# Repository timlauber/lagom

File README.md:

# lagom
Lagom is an easy to build 65% keyboard using ~~only~~ some through hole components. It uses a separate microcontroller (like the Pro Micro, Elite C or something RP2040 based) to enable flexibility in firmware and connectivity and to further simplify the soldering experience (no more tricksy USB ports). Demultiplexers and a custom matrix are used to enable the size and features of the board with only the pinouts of a pro micro.

## Changes
This version replaces most trough hole components for SMD variants, but keeps visuals. A power switch as well as a battery connector is added for full wireless support. Only ISO layout is supported.

**Original lagom kits are available for sale at [sthlmkb.com](https://sthlmkb.com/shop/lagom-keyboard-kit/)**

[License](LICENSE)

Lagom is licensed under the [Creative Commons Attribution-NonCommercial 4.0 International license](https://creativecommons.org/licenses/by-nc/4.0/). This design as it stands in this repository may be freely reproduced, modified, and manufactured for PERSONAL USE ONLY and may not be reproduced in physical form for public sale. 

## Features
* ~~Only through hole components for easy soldering~~
* Separate microcontroller using Pro micro, Elite C, Nice! Nano or equivalent footprint. So micro USB, USB-C or Bluetooth are all options!
* 2 rotary encoders
* OLED screen
* Optional underglow RGB lighting with a WS2812b light strip
* ~~Multiple layout options including ISO, ANSI, split space (2.25u + 1.25u + 2.75u), 7u space, split left shift (1.25u + 1u) and stepped capslock ([layout]("http://www.keyboard-layout-editor.com/##@_name=Lagom&notes=16%20cols%20%2F=%204%20pins%20with%202x%203%20to%208%20demux%20(2%5E4%20%2F=%2016)%0A5%20rows%0A11%20pins%20total%20for%20keyswitches%0A16%20+%202%20pins%20(for%20OLED)%20on%20a%20pro%20micro%0A1%20pin%20for%20LED%20underglow%0A4%20pins%20for%202%20encoders%0A%0A72%20keys%20+%202%20enc%20%3B&@_x:13.75%3B&=1,15&_x:0.25%3B&=2,15&_x:0.25%3B&=0,0%0A%0A%0A%0A%0A%0A%0A%0A%0Ae&=0,1%0A%0A%0A%0A%0A%0A%0A%0A%0Ae%3B&@_y:0.25%3B&=0,0&=0,1&=0,2&=0,3&=0,4&=0,5&=0,6&=0,7&=0,8&=0,9&=0,10&=0,11&=0,12&_w:2%3B&=0,14%0A%0A%0A0,0&=0,15&_x:0.25%3B&=1,0%0A%0A%0A%0A%0A%0A%0A%0A%0Ae&=1,1%0A%0A%0A%0A%0A%0A%0A%0A%0Ae%3B&@_w:1.5%3B&=1,0&=1,1&=1,2&=1,3&=1,4&=1,5&=1,6&=1,7&=1,8&=1,9&=1,10&=1,11&=1,12&_w:1.5%3B&=1,13%0A%0A%0A1,0&=1,14%3B&@_w:1.75%3B&=2,0&=2,1&=2,2&=2,3&=2,4&=2,5&=2,6&=2,7&=2,8&=2,9&=2,10&=2,11&_w:2.25%3B&=2,13%0A%0A%0A1,0&=2,14%3B&@_w:2.25%3B&=3,0%0A%0A%0A2,0&=3,2&=3,3&=3,4&=3,5&=3,6&=3,7&=3,8&=3,9&=3,10&=3,11&_w:1.75%3B&=3,12&=3,13&=3,14%3B&@_w:1.25%3B&=4,0%0A%0A%0A3,0&_w:1.25%3B&=4,1%0A%0A%0A3,0&_w:1.25%3B&=4,2%0A%0A%0A3,0&_w:6.25%3B&=4,6%0A%0A%0A3,0&_w:1.25%3B&=4,10%0A%0A%0A3,0&_w:1.25%3B&=4,11%0A%0A%0A3,0&_x:0.5%3B&=4,12&=4,13&=4,14%3B&@_y:0.5&w:1.25%3B&=4,0%0A%0A%0A3,1&_w:1.25%3B&=4,1%0A%0A%0A3,1&_w:1.25%3B&=4,2%0A%0A%0A3,1&_w:2.25%3B&=4,4%0A%0A%0A3,1&_w:1.25%3B&=4,6%0A%0A%0A3,1&_w:2.75%3B&=4,8%0A%0A%0A3,1&_w:1.25%3B&=4,10%0A%0A%0A3,1&_w:1.25%3B&=4,11%0A%0A%0A3,1%3B&@_y:-0.25&x:15&w:1.25&h:2&w2:1.5&h2:1&x2:-0.25%3B&=2,13%0A%0A%0A1,1%3B&@_y:-0.75&w:1.5%3B&=4,0%0A%0A%0A3,2&=4,1%0A%0A%0A3,2&_w:1.5%3B&=4,2%0A%0A%0A3,2&_w:7%3B&=4,6%0A%0A%0A3,2&_w:1.5%3B&=4,11%0A%0A%0A3,2%3B&@_y:-0.25&x:14%3B&=2,12%0A%0A%0A1,1%3B&@_w:1.25%3B&=3,0%0A%0A%0A2,1&=3,1%0A%0A%0A2,1&_x:9.75%3B&=0,13%0A%0A%0A0,1&=0,14%0A%0A%0A0,1"))~~
* Open and visible components (in the style of Plaid, Romac etc)
* Simple, beautiful and flexible sandwich case out of FR4 (pcb material)

## Components required - To be determined!
* PCB
* FR4 Switch plate
* FR4 Base 
* Controller (I used a Pro Micro in the guide but anything that shares the footprint and pinout will be fine e.g. Elite C, Nice! Nano, or something RP2040 powered!)
* Diodes 1N4148 (74)
* 0.1μF Capacitor (2)
* 16 pin IC socket (2)
* IC (74HC138N) demultiplexer (2)
* Switches (5 pin MX footprint) (up to 72 depending on layout)
* Rotary encoders (2)
* Rotary encoder knobs (2)
* 0.91" OLED screen
* 10mm M2 Standoffs (9 required if mounting the base to the plate)
* 6mm x M2 screws for attaching the standoffs to the plate/base (2 per standoff so 18 total)
* Acrylic cover for the components at the top (optional, not included)
* Stabilisers (PCB mount) (5 x 2u or 3 x 2u + 6.25u or 3 x 2u + 7u depending on layout)
* Rubber feet for the base

Build guide for this version is not available.
[Original build guide available here](https://github.com/mohoyt/lagom/blob/main/build_guide.md)

## Known issues 
None yet! 

## Where to buy
Lagom kits are available for sale exclusively at [sthlmkb.com](https://sthlmkb.com/shop/lagom-keyboard-kit/)

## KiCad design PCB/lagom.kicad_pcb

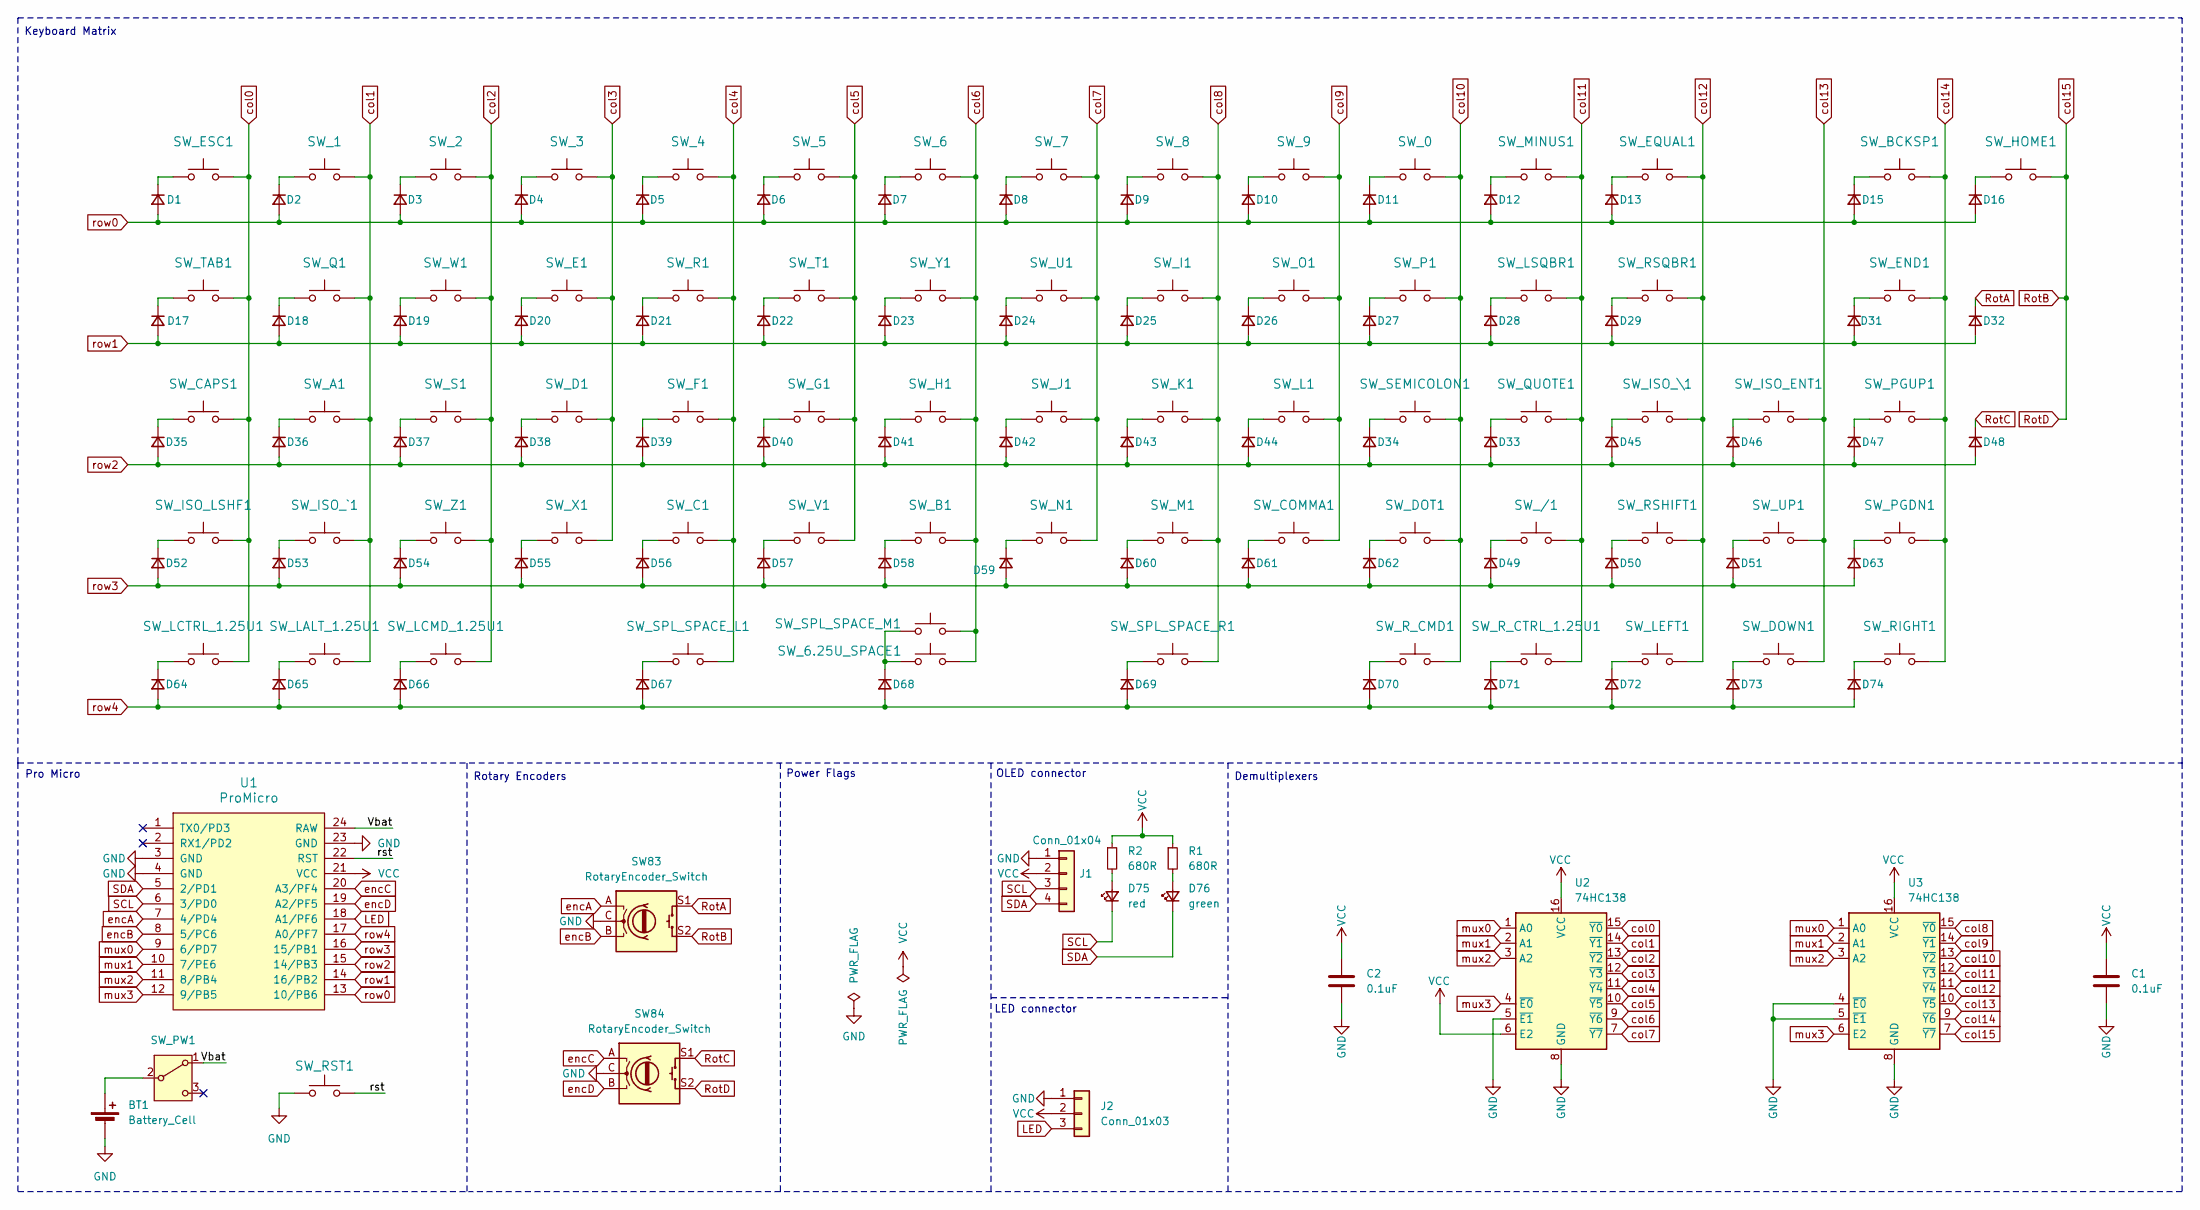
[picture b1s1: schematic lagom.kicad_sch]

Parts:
BT1: Battery_Cell; JST_PH_S2B-PH-K_1x02_P2.00mm_Horizontal
C1, C2: 0.1uF; C_0805_2012Metric
D1, D2, D3, D4, D5, D6, D7, D8, D9, D10, D11, D12, D13, D15, D16, D17, D18, D19, D20, D21, D22, D23, D24, D25, D26, D27, D28, D29, D31, D32, D33, D34, D35, D36, D37, D38, D39, D40, D41, D42, D43, D44, D45, D46, D47, D48, D49, D50, D51, D52, D53, D54, D55, D56, D57, D58, D59, D60, D61, D62, D63, D64, D65, D66, D67, D68, D69, D70, D71, D72, D73, D74: 1N4148; D_MiniMELF_noSilk
D75: red; LED_1206_3216Metric
D76: green; LED_1206_3216Metric
J1: Conn_01x04; PinSocket_1x04_P2.54mm_Vertical
J2: Conn_01x03; PinSocket_1x03_P2.54mm_Vertical
R1, R2: 680R; R_1206_3216Metric
SW83, SW84: RotaryEncoder_Switch; RotaryEncoder_Alps_EC11E-Switch_Vertical_H20mm
SW_0, SW_1, SW_2, SW_3, SW_4, SW_5, SW_6, SW_7, SW_8, SW_9: KEYSW; SW_Kailh_HotSwap_1.00u_PCB
SW_6.25U_SPACE1: KEYSW; SW_Kailh_HotSwap_6.25u_PCB_reverse
SW_/1: KEYSW; SW_Kailh_HotSwap_1.00u_PCB
SW_A1: KEYSW; SW_Kailh_HotSwap_1.00u_PCB
SW_B1: KEYSW; SW_Kailh_HotSwap_1.00u_PCB
SW_BCKSP1: KEYSW; SW_Kailh_HotSwap_2.00u_PCB
SW_C1: KEYSW; SW_Kailh_HotSwap_1.00u_PCB
SW_CAPS1: KEYSW; SW_Kailh_HotSwap_1.75u_PCB
SW_COMMA1: KEYSW; SW_Kailh_HotSwap_1.00u_PCB
SW_D1: KEYSW; SW_Kailh_HotSwap_1.00u_PCB
SW_DOT1: KEYSW; SW_Kailh_HotSwap_1.00u_PCB
SW_DOWN1: KEYSW; SW_Kailh_HotSwap_1.00u_PCB
SW_E1: KEYSW; SW_Kailh_HotSwap_1.00u_PCB
SW_END1: KEYSW; SW_Kailh_HotSwap_1.00u_PCB
SW_EQUAL1: KEYSW; SW_Kailh_HotSwap_1.00u_PCB
SW_ESC1: KEYSW; SW_Kailh_HotSwap_1.00u_PCB
SW_F1: KEYSW; SW_Kailh_HotSwap_1.00u_PCB
SW_G1: KEYSW; SW_Kailh_HotSwap_1.00u_PCB
SW_H1: KEYSW; SW_Kailh_HotSwap_1.00u_PCB
SW_HOME1: KEYSW; SW_Kailh_HotSwap_1.00u_PCB
SW_I1: KEYSW; SW_Kailh_HotSwap_1.00u_PCB
SW_ISO_ENT1: KEYSW; SW_Kailh_HotSwap_ISOEnter_PCB
SW_ISO_LSHF1: KEYSW; SW_Kailh_HotSwap_1.25u_PCB
SW_ISO_\1: KEYSW; SW_Kailh_HotSwap_1.00u_PCB
SW_ISO_`1: KEYSW; SW_Kailh_HotSwap_1.00u_PCB
SW_J1: KEYSW; SW_Kailh_HotSwap_1.00u_PCB
SW_K1: KEYSW; SW_Kailh_HotSwap_1.00u_PCB
SW_L1: KEYSW; SW_Kailh_HotSwap_1.00u_PCB
SW_LALT_1.25U1: KEYSW; SW_Kailh_HotSwap_1.25u_PCB
SW_LCMD_1.25U1: KEYSW; SW_Kailh_HotSwap_1.25u_PCB
SW_LCTRL_1.25U1: KEYSW; SW_Kailh_HotSwap_1.25u_PCB
SW_LEFT1: KEYSW; SW_Kailh_HotSwap_1.00u_PCB
SW_LSQBR1: KEYSW; SW_Kailh_HotSwap_1.00u_PCB
SW_M1: KEYSW; SW_Kailh_HotSwap_1.00u_PCB
SW_MINUS1: KEYSW; SW_Kailh_HotSwap_1.00u_PCB
SW_N1: KEYSW; SW_Kailh_HotSwap_1.00u_PCB
SW_O1: KEYSW; SW_Kailh_HotSwap_1.00u_PCB
SW_P1: KEYSW; SW_Kailh_HotSwap_1.00u_PCB
SW_PGDN1: KEYSW; SW_Kailh_HotSwap_1.00u_PCB
SW_PGUP1: KEYSW; SW_Kailh_HotSwap_1.00u_PCB
SW_PW1: SW_SPDT; PinHeader_1x03_P2.54mm_Vertical
SW_Q1: KEYSW; SW_Kailh_HotSwap_1.00u_PCB
SW_QUOTE1: KEYSW; SW_Kailh_HotSwap_1.00u_PCB
SW_R1: KEYSW; SW_Kailh_HotSwap_1.00u_PCB
SW_RIGHT1: KEYSW; SW_Kailh_HotSwap_1.00u_PCB
SW_RSHIFT1: KEYSW; SW_Kailh_HotSwap_1.75u_PCB
SW_RSQBR1: KEYSW; SW_Kailh_HotSwap_1.00u_PCB
SW_RST1: KEYSW; SW_PUSH_1P1T_6x3.5mm_H5.0_APEM_MJTP1250
SW_R_CMD1: KEYSW; SW_Kailh_HotSwap_1.25u_PCB
SW_R_CTRL_1.25U1: KEYSW; SW_Kailh_HotSwap_1.25u_PCB
SW_S1: KEYSW; SW_Kailh_HotSwap_1.00u_PCB
SW_SEMICOLON1: KEYSW; SW_Kailh_HotSwap_1.00u_PCB
SW_SPL_SPACE_L1: KEYSW; SW_Kailh_HotSwap_2.25u_PCB_reverse
SW_SPL_SPACE_M1: KEYSW; SW_Kailh_HotSwap_1.25u_PCB
SW_SPL_SPACE_R1: KEYSW; SW_Kailh_HotSwap_2.75u_PCB_reverse
SW_T1: KEYSW; SW_Kailh_HotSwap_1.00u_PCB
SW_TAB1: KEYSW; SW_Kailh_HotSwap_1.50u_PCB
SW_U1: KEYSW; SW_Kailh_HotSwap_1.00u_PCB
SW_UP1: KEYSW; SW_Kailh_HotSwap_1.00u_PCB
SW_V1: KEYSW; SW_Kailh_HotSwap_1.00u_PCB
SW_W1: KEYSW; SW_Kailh_HotSwap_1.00u_PCB
SW_X1: KEYSW; SW_Kailh_HotSwap_1.00u_PCB
SW_Y1: KEYSW; SW_Kailh_HotSwap_1.00u_PCB
SW_Z1: KEYSW; SW_Kailh_HotSwap_1.00u_PCB
U1: ProMicro; ArduinoProMicro-ZigZag
U2, U3: 74HC138; SOIC-16_3.9x9.9mm_P1.27mm

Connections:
/Vbat: SW_PW1.1 (A), U1.24 (RAW)
/rst: SW_RST1.2, U1.22 (RST)
GND: BT1.2 (-), C1.2, C2.2, J1.1, J2.1, SW83.C, SW84.C, SW_RST1.1, U1.3 (GND), U1.4 (GND), U1.23 (GND), U2.5 (~E1), U2.8 (GND), U3.4 (~E0), U3.5 (~E1), U3.8 (GND)
LED: J2.3, U1.18 (A1/PF6)
unnamed: BT1.1 (+), SW_PW1.2 (B)
unnamed: D1.1 (K), SW_ESC1.1
unnamed: D2.1 (K), SW_1.1
unnamed: D3.1 (K), SW_2.1
unnamed: D4.1 (K), SW_3.1
unnamed: D5.1 (K), SW_4.1
unnamed: D6.1 (K), SW_5.1
unnamed: D7.1 (K), SW_6.1
unnamed: D8.1 (K), SW_7.1
unnamed: D9.1 (K), SW_8.1
unnamed: D10.1 (K), SW_9.1
unnamed: D11.1 (K), SW_0.1
unnamed: D12.1 (K), SW_MINUS1.1
unnamed: D13.1 (K), SW_EQUAL1.1
unnamed: D15.1 (K), SW_BCKSP1.1
unnamed: D16.1 (K), SW_HOME1.1
unnamed: D17.1 (K), SW_TAB1.1
unnamed: D18.1 (K), SW_Q1.1
unnamed: D19.1 (K), SW_W1.1
unnamed: D20.1 (K), SW_E1.1
unnamed: D21.1 (K), SW_R1.1
unnamed: D22.1 (K), SW_T1.1
unnamed: D23.1 (K), SW_Y1.1
unnamed: D24.1 (K), SW_U1.1
unnamed: D25.1 (K), SW_I1.1
unnamed: D26.1 (K), SW_O1.1
unnamed: D27.1 (K), SW_P1.1
unnamed: D28.1 (K), SW_LSQBR1.1
unnamed: D29.1 (K), SW_RSQBR1.1
unnamed: D31.1 (K), SW_END1.1
unnamed: D33.1 (K), SW_QUOTE1.1
unnamed: D34.1 (K), SW_SEMICOLON1.1
unnamed: D35.1 (K), SW_CAPS1.1
unnamed: D36.1 (K), SW_A1.1
unnamed: D37.1 (K), SW_S1.1
unnamed: D38.1 (K), SW_D1.1
unnamed: D39.1 (K), SW_F1.1
unnamed: D40.1 (K), SW_G1.1
unnamed: D41.1 (K), SW_H1.1
unnamed: D42.1 (K), SW_J1.1
unnamed: D43.1 (K), SW_K1.1
unnamed: D44.1 (K), SW_L1.1
unnamed: D45.1 (K), SW_ISO_\1.1
unnamed: D46.1 (K), SW_ISO_ENT1.1
unnamed: D47.1 (K), SW_PGUP1.1
unnamed: D49.1 (K), SW_/1.1
unnamed: D50.1 (K), SW_RSHIFT1.1
unnamed: D51.1 (K), SW_UP1.1
unnamed: D52.1 (K), SW_ISO_LSHF1.1
unnamed: D53.1 (K), SW_ISO_`1.1
unnamed: D54.1 (K), SW_Z1.1
unnamed: D55.1 (K), SW_X1.1
unnamed: D56.1 (K), SW_C1.1
unnamed: D57.1 (K), SW_V1.1
unnamed: D58.1 (K), SW_B1.1
unnamed: D59.1 (K), SW_N1.1
unnamed: D60.1 (K), SW_M1.1
unnamed: D61.1 (K), SW_COMMA1.1
unnamed: D62.1 (K), SW_DOT1.1
unnamed: D63.1 (K), SW_PGDN1.1
unnamed: D64.1 (K), SW_LCTRL_1.25U1.1
unnamed: D65.1 (K), SW_LALT_1.25U1.1
unnamed: D66.1 (K), SW_LCMD_1.25U1.1
unnamed: D67.1 (K), SW_SPL_SPACE_L1.1
unnamed: D68.1 (K), SW_6.25U_SPACE1.1, SW_SPL_SPACE_M1.2
unnamed: D69.1 (K), SW_SPL_SPACE_R1.1
unnamed: D70.1 (K), SW_R_CMD1.1
unnamed: D71.1 (K), SW_R_CTRL_1.25U1.1
unnamed: D72.1 (K), SW_LEFT1.1
unnamed: D73.1 (K), SW_DOWN1.1
unnamed: D74.1 (K), SW_RIGHT1.1
unnamed: D75.2 (A), R2.2
unnamed: D76.2 (A), R1.2
RotA: D32.1 (K), SW83.S1
RotB: SW83.S2, SW84.S2, SW_HOME1.2, U3.7 (~Y7)
RotC: D48.1 (K), SW84.S1
SCL: D75.1 (K), J1.3, U1.6 (3/PD0)
SDA: D76.1 (K), J1.4, U1.5 (2/PD1)
VCC: C1.1, C2.1, J1.2, J2.2, R1.1, R2.1, U1.21 (VCC), U2.6 (E2), U2.16 (VCC), U3.16 (VCC)
col0: SW_CAPS1.2, SW_ESC1.2, SW_ISO_LSHF1.2, SW_LCTRL_1.25U1.2, SW_TAB1.2, U2.15 (~Y0)
col1: SW_1.2, SW_A1.2, SW_ISO_`1.2, SW_LALT_1.25U1.2, SW_Q1.2, U2.14 (~Y1)
col2: SW_2.2, SW_LCMD_1.25U1.2, SW_S1.2, SW_W1.2, SW_Z1.2, U2.13 (~Y2)
col3: SW_3.2, SW_D1.2, SW_E1.2, SW_X1.2, U2.12 (~Y3)
col4: SW_4.2, SW_C1.2, SW_F1.2, SW_R1.2, SW_SPL_SPACE_L1.2, U2.11 (~Y4)
col5: SW_5.2, SW_G1.2, SW_T1.2, SW_V1.2, U2.10 (~Y5)
col6: SW_6.2, SW_6.25U_SPACE1.2, SW_B1.2, SW_H1.2, SW_SPL_SPACE_M1.1, SW_Y1.2, U2.9 (~Y6)
col7: SW_7.2, SW_J1.2, SW_N1.2, SW_U1.2, U2.7 (~Y7)
col8: SW_8.2, SW_I1.2, SW_K1.2, SW_M1.2, SW_SPL_SPACE_R1.2, U3.15 (~Y0)
col9: SW_9.2, SW_COMMA1.2, SW_L1.2, SW_O1.2, U3.14 (~Y1)
col10: SW_0.2, SW_DOT1.2, SW_P1.2, SW_R_CMD1.2, SW_SEMICOLON1.2, U3.13 (~Y2)
col11: SW_/1.2, SW_LSQBR1.2, SW_MINUS1.2, SW_QUOTE1.2, SW_R_CTRL_1.25U1.2, U3.12 (~Y3)
col12: SW_EQUAL1.2, SW_ISO_\1.2, SW_LEFT1.2, SW_RSHIFT1.2, SW_RSQBR1.2, U3.11 (~Y4)
col13: SW_DOWN1.2, SW_ISO_ENT1.2, SW_UP1.2, U3.10 (~Y5)
col14: SW_BCKSP1.2, SW_END1.2, SW_PGDN1.2, SW_PGUP1.2, SW_RIGHT1.2, U3.9 (~Y6)
encA: SW83.A, U1.7 (4/PD4)
encB: SW83.B, U1.8 (5/PC6)
encC: SW84.A, U1.20 (A3/PF4)
encD: SW84.B, U1.19 (A2/PF5)
mux0: U1.9 (6/PD7), U2.1 (A0), U3.1 (A0)
mux1: U1.10 (7/PE6), U2.2 (A1), U3.2 (A1)
mux2: U1.11 (8/PB4), U2.3 (A2), U3.3 (A2)
mux3: U1.12 (9/PB5), U2.4 (~E0), U3.6 (E2)
row0: D1.2 (A), D2.2 (A), D3.2 (A), D4.2 (A), D5.2 (A), D6.2 (A), D7.2 (A), D8.2 (A), D9.2 (A), D10.2 (A), D11.2 (A), D12.2 (A), D13.2 (A), D15.2 (A), D16.2 (A), U1.13 (10/PB6)
row1: D17.2 (A), D18.2 (A), D19.2 (A), D20.2 (A), D21.2 (A), D22.2 (A), D23.2 (A), D24.2 (A), D25.2 (A), D26.2 (A), D27.2 (A), D28.2 (A), D29.2 (A), D31.2 (A), D32.2 (A), U1.14 (16/PB2)
row2: D33.2 (A), D34.2 (A), D35.2 (A), D36.2 (A), D37.2 (A), D38.2 (A), D39.2 (A), D40.2 (A), D41.2 (A), D42.2 (A), D43.2 (A), D44.2 (A), D45.2 (A), D46.2 (A), D47.2 (A), D48.2 (A), U1.15 (14/PB3)
row3: D49.2 (A), D50.2 (A), D51.2 (A), D52.2 (A), D53.2 (A), D54.2 (A), D55.2 (A), D56.2 (A), D57.2 (A), D58.2 (A), D59.2 (A), D60.2 (A), D61.2 (A), D62.2 (A), D63.2 (A), U1.16 (15/PB1)
row4: D64.2 (A), D65.2 (A), D66.2 (A), D67.2 (A), D68.2 (A), D69.2 (A), D70.2 (A), D71.2 (A), D72.2 (A), D73.2 (A), D74.2 (A), U1.17 (A0/PF7)

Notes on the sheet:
OLED connector
Rotary Encoders
Keyboard Matrix
Power Flags
LED connector
Pro Micro
Demultiplexers

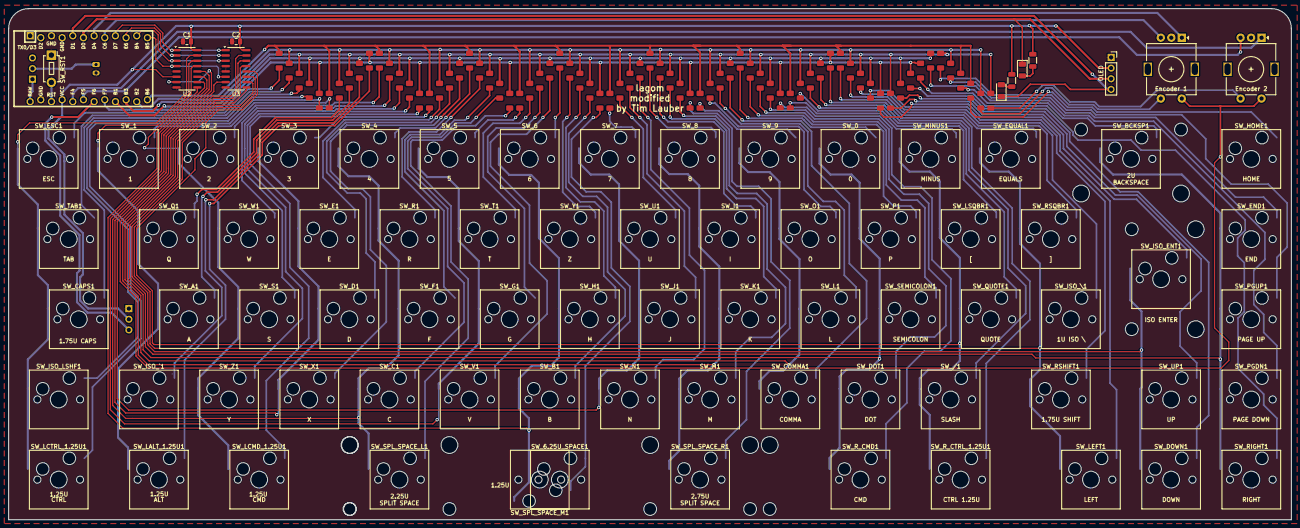
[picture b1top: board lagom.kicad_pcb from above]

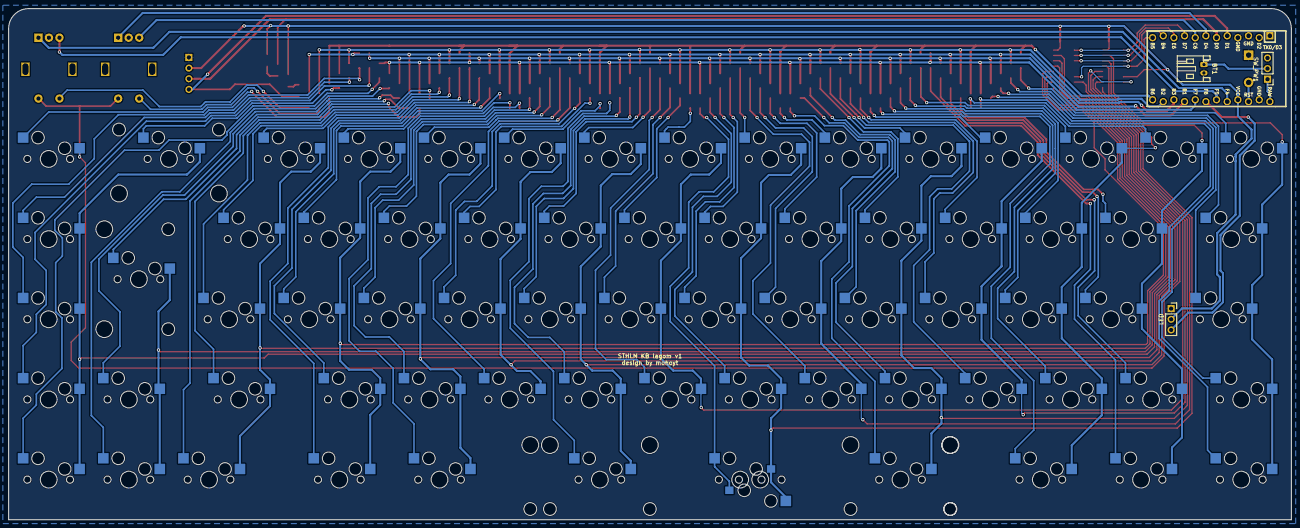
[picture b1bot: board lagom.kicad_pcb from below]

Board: 2 copper layers, 305.6 x 121.8 mm, 159 parts (4 on the bottom side), 111 nets.

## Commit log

2024-07-31 Remove legacy build guide
2024-07-31 Remove legacy firmware section
2024-07-31 Remove legacy gerber outputs
2024-07-31 Update main pcb kicad to KiCAD8
2024-07-31 Remove legacy KiCAD backups and dont version them anymore
2024-07-31 Replace 74hc138 symbol with standard library symbol and remove custom library
2024-07-31 Demultiplexer footprint -> TSSOP16
2024-07-31 Remove unused symbol libraries from library table
2024-07-31 Remove optional ANSI from schematic
2024-07-31 Standard SW_PUSH symbol. Remove unused library and submodule
2024-07-31 Add battery connector, reset and power switch to schematic
2024-07-31 Remove symbol libraries from footprint library table
2024-08-01 All Diodes 1N4148 type
2024-08-01 Capacitor fp -> 0805
2024-08-01 main schematic: Change switch footprints to hotswap, add custom switch fp library
2024-08-01 Change promicro symbol to local and remove dependency of keebio sym lib
2024-08-01 Layout - Cleanup pre fottprint update
2024-08-01 Schematic - Diode fp -> SMD MiniMELF
2024-08-08 Layout - Complete rework
2024-08-09 Add alternative LEDs instead of OLED
2024-08-09 Remove unused external fp library
2024-08-11 Remove unused git submodule
2024-08-11 plate pcb -> kicad v8
2024-08-11 plate - Remove section for oled and rotary encoder.
2024-08-11 Cleanup outline
2024-08-15 Change mounting equipment to M3 Hole + SMSI solder nuts
2024-08-20 Remove legacy base and plate gerber files
2024-08-20 Add fabrication outputs
2024-08-20 Add signature
